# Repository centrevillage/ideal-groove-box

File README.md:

# ideal-groove-box
The GrooveBox for me, and everyone.

~~下記ページに開発Slackの招待リンクがあります。~~
~~どなたでもご自由にご参加ください！~~

~~[開発に参加する方へ](https://github.com/centrevillage/ideal-groove-box/wiki/%E9%96%8B%E7%99%BA%E3%81%AB%E5%8F%82%E5%8A%A0%E3%81%99%E3%82%8B%E6%96%B9%E3%81%B8)~~

2024年12月よりdiscordにてプロジェクト再始動しました。

[ideal groove box project](https://discord.gg/Y8a6y2wYff)

設計思想も変わっているので、こちらのリポジトリはどこかのタイミングで整理する予定です。

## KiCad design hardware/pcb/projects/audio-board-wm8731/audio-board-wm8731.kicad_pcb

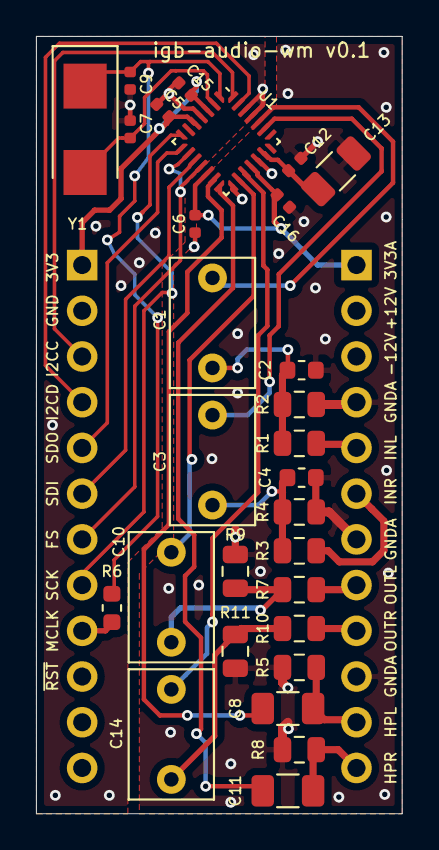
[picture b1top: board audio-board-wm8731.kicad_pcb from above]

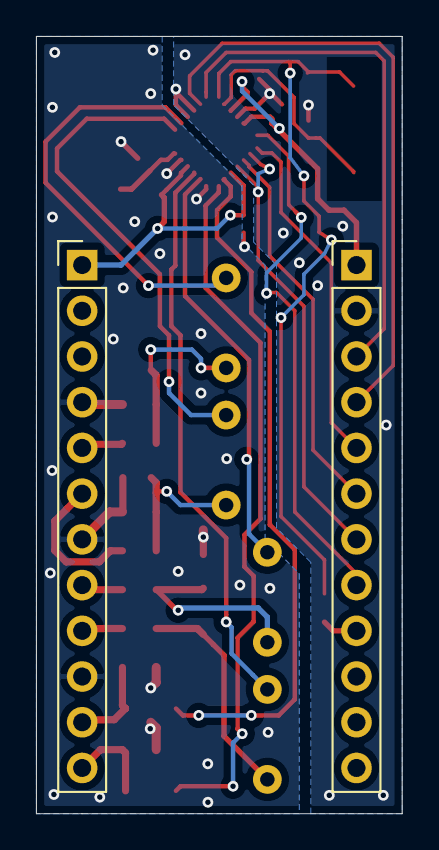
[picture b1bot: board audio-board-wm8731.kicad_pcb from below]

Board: 2 copper layers, 20.3 x 43.2 mm, 31 parts (2 on the bottom side), 30 nets.

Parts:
C1, C3, C10, C14: 1u; C_Rect_L7.0mm_W4.5mm_P5.00mm
C2, C4: 220p; C_0603_1608Metric
C5, C6, C12, C15, C16: 100n; C_0402_1005Metric
C7, C9: 18p; C_0402_1005Metric
C8, C11: 100u; C_1206_3216Metric
C13: 10u; C_1206_3216Metric
J1, J2: Conn_01x12; PinHeader_1x12_P2.54mm_Vertical
R1, R2, R3, R4: 10k; R_0805_2012Metric
R5, R8, R9, R11: 100k; R_0805_2012Metric
R6: 0; R_0603_1608Metric
R7, R10: 100; R_0805_2012Metric
U1: wm8731_qfn; QFN-28_4x4mm_P0.5mm
Y1: 12.288MHz; Crystal_SMD_Abracon_ABM3-2pin_5.0x3.2mm_hand

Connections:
+3.3VA: C6.2, C16.2, J1.1, U1.12, U1.18
+3V3: C5.2, C15.2, J2.1, U1.3, U1.5
/ADC_L: C1.2, U1.24
/ADC_R: C3.2, U1.23
/DAC_L: C10.2, U1.16
/DAC_R: C14.2, U1.17
/HP_OUT_L: C8.2, J1.11, R5.2
/HP_OUT_R: C11.2, J1.12, R8.2
/I2C_SCL: J2.3, U1.28
/I2C_SDA: J2.4, U1.27
/I2S_FS: J2.7, U1.9, U1.11
/I2S_MCLK: J2.9, R6.1
/I2S_SCK: J2.8, U1.7
/I2S_SDI: J2.6, U1.10
/I2S_SDO: J2.5, U1.8
/LINE_IN_L: J1.5, R1.2
/LINE_IN_R: J1.6, R3.2
/LINE_OUT_L: J1.8, R7.2
/LINE_OUT_R: J1.9, R10.2
GND: C5.1, C7.2, C9.2, C15.1, J2.2, U1.4, U1.25, U1.26
GNDA: C2.1, C4.1, C6.1, C12.2, C13.2, C16.1, J1.4, J1.7, J1.10, R2.2, R4.2, R5.1, R8.1, R9.1, R11.1, U1.15, U1.19
unnamed: C1.1, C2.2, R1.1, R2.1
unnamed: C3.1, C4.2, R3.1, R4.1
unnamed: C7.1, U1.2, Y1.2
unnamed: C8.1, U1.13
unnamed: C9.1, R6.2, U1.1, Y1.1
unnamed: C10.1, R7.1, R9.2
unnamed: C11.1, U1.14
unnamed: C12.1, C13.1, U1.20
unnamed: C14.1, R10.1, R11.2

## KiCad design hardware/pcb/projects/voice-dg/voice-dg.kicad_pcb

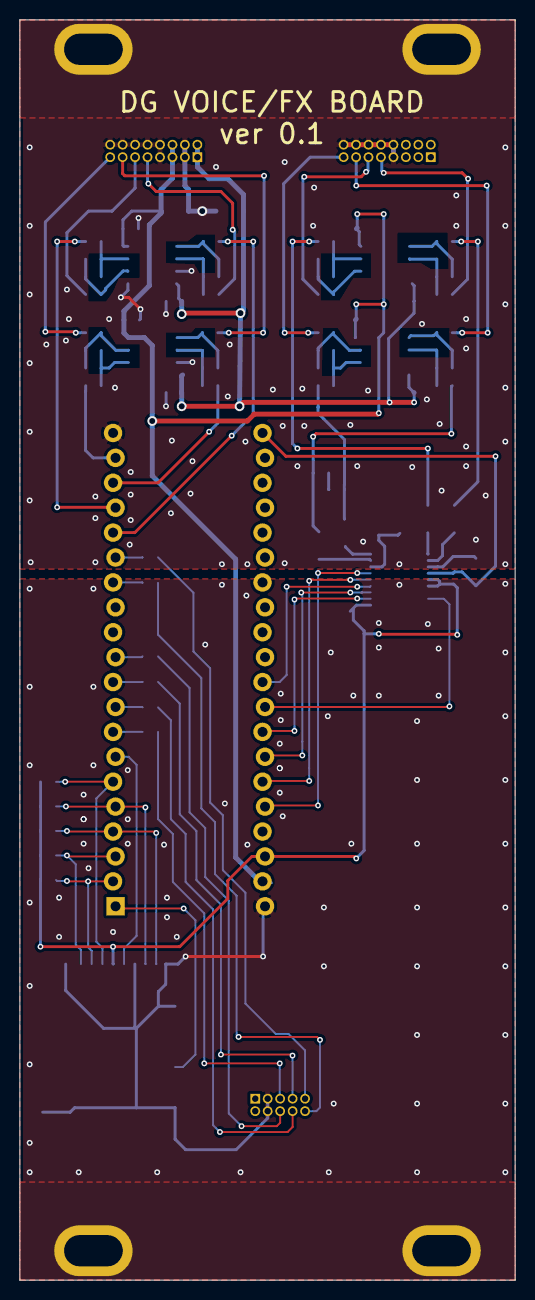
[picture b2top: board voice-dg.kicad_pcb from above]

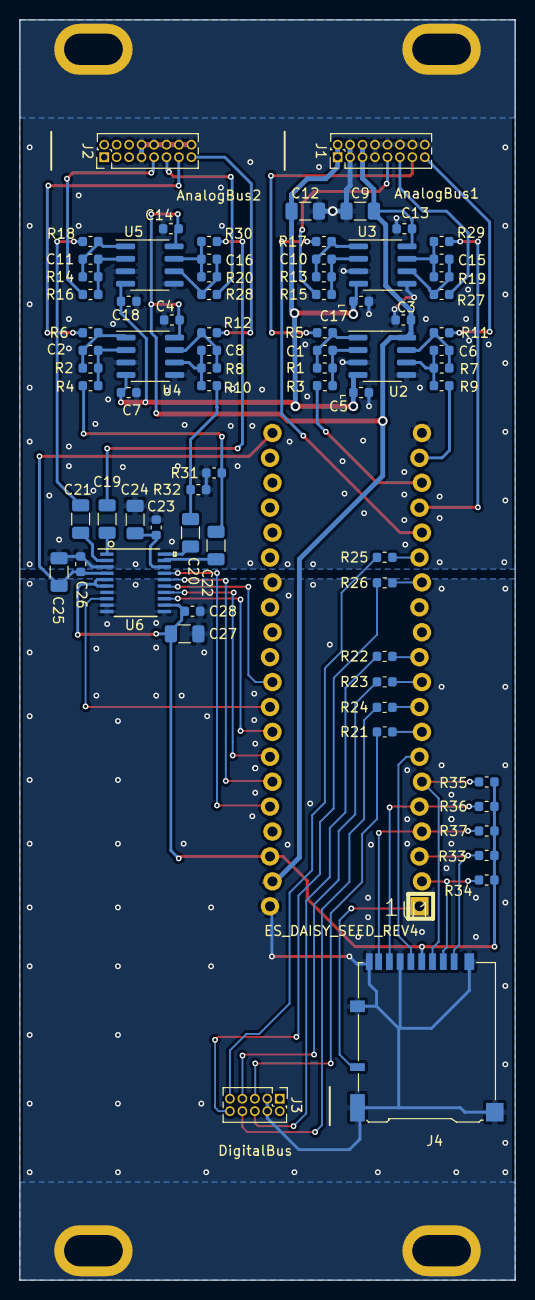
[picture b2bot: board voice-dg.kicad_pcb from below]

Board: 2 copper layers, 50.5 x 128.5 mm, 75 parts (75 on the bottom side), 68 nets.

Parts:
C1, C2, C6, C8, C10, C11, C15, C16: 12p; C_0603_1608Metric
C3, C4, C5, C7, C13, C14, C17, C18, C23, C26, C28: 100n; C_0603_1608Metric
C9, C12: 22u; C_1206_3216Metric
C19, C20, C21, C22, C25, C27: 10u; C_1206_3216Metric
C24: 2.2u; C_1206_3216Metric
J1: AnalogBus; PinHeader_2x08_P1.27mm_Vertical
J2: AnalogBusEx; PinHeader_2x08_P1.27mm_Vertical
J3: DigitalBus; PinHeader_2x05_P1.27mm_Vertical
J4: Micro_SD_Card_Det_Hirose_DM3AT; microSD_HC_Hirose_DM3AT-SF-PEJM5_hand
R1, R2, R7, R8, R15, R16, R27, R28: 100k; R_0603_1608Metric
R3, R4, R9, R10, R13, R14, R19, R20: 10k; R_0603_1608Metric
R5, R6, R11, R12, R17, R18, R29, R30: 470; R_0603_1608Metric
R21, R22, R23, R24, R25, R26: 47; R_0603_1608Metric
R31, R32, R33, R34, R35, R36, R37: 47k; R_0603_1608Metric
U1: ES_DAISY_SEED_REV4; ES_DAISY_SEED
U2, U3, U4, U5: OPA2134; SOIC-8_3.9x4.9mm_P1.27mm
U6: AK4556VT

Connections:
+3.3VA: C25.2, C26.1, U1.21, U6.4
+3V3: C27.2, C28.1, J4.4, R33.2, R34.2, R35.2, R36.2, R37.2, U1.38, U6.5, U6.6, U6.12
+12V: C3.1, C4.1, C9.2, C13.1, C14.1, J1.5, J1.6, U1.39, U2.8, U3.8, U4.8, U5.8
-12V: C5.1, C7.1, C12.1, C17.1, C18.1, J1.1, J1.2, U2.4, U3.4, U4.4, U5.4
/AK4556_RST: U1.36, U6.17
/AnalogIn1: J1.9, R15.2
/AnalogIn2: J1.11, R27.2
/AnalogIn3: J2.9, R16.2
/AnalogIn4: J2.11, R28.2
/AnalogOut1: J1.13, R5.1
/AnalogOut2: J1.15, R11.1
/AnalogOut3: J2.13, R6.1
/AnalogOut4: J2.15, R12.1
/DG_AUDIO_IN_L: R17.1, U1.16
/DG_AUDIO_IN_R: R29.1, U1.17
/DG_AUDIO_OUT_L: R3.2, U1.18
/DG_AUDIO_OUT_R: R9.2, U1.19
/EX_AUDIO_IN_L: C21.1, R18.1
/EX_AUDIO_IN_R: C19.1, R30.1
/EX_AUDIO_OUT_L: C22.2, R4.2, R31.2
/EX_AUDIO_OUT_R: C20.2, R10.2, R32.2
/SAI2_FS_B: U1.34, U6.14
/SAI2_MCLK_B: U1.31, U6.15
/SAI2_SCK_B: U1.35, U6.16
/SAI2_SD_A: U1.33, U6.13
/SAI2_SD_B: U1.32, U6.8
/SD_CLK: J4.5, U1.7
/SD_CMD: J4.3, R35.1, U1.6
/SD_D0: J4.7, R36.1, U1.5
/SD_D1: J4.8, R37.1, U1.4
/SD_D2: J4.1, R33.1, U1.3
/SD_D3: J4.2, R34.1, U1.2
/SPI_MISO: R23.2, U1.10
/SPI_MOSI: R22.1, U1.11
/SPI_SCK: R24.1, U1.9
/USART_RX: R25.2, U1.15
/USART_TX: R26.1, U1.14
/~SD_SW: J4.10, U1.1
/~SPI_CS: R21.2, U1.8
GND: C27.1, C28.2, J3.3, J3.4, J4.6, J4.9, J4.11, U1.40, U6.7, U6.9, U6.10, U6.11
GNDA: C3.2, C4.2, C5.2, C7.2, C9.1, C12.2, C13.2, C14.2, C17.2, C18.2, C23.2, C24.1, C25.1, C26.2, J1.3, J1.4, J1.7, J1.8, J1.10, J1.12, J1.14, J1.16, J2.7, J2.8, J2.10, J2.12, J2.14, J2.16, R31.1, R32.1, U1.20, U2.3, U2.5, U3.3, U3.5, U4.3, U4.5, U5.3, U5.5, U6.3
unnamed: C1.1, R1.1, R5.2, U2.1
unnamed: C1.2, R1.2, R3.1, U2.2
unnamed: C2.1, R2.1, R6.2, U4.1
unnamed: C2.2, R2.2, R4.1, U4.2
unnamed: C6.1, R7.1, R11.2, U2.7
unnamed: C6.2, R7.2, R9.1, U2.6
unnamed: C8.1, R8.1, R12.2, U4.7
unnamed: C8.2, R8.2, R10.1, U4.6
unnamed: C10.1, R13.1, R17.2, U3.1
unnamed: C10.2, R13.2, R15.1, U3.2
unnamed: C11.1, R14.1, R18.2, U5.1
unnamed: C11.2, R14.2, R16.1, U5.2
unnamed: C15.1, R19.1, R29.2, U3.7
unnamed: C15.2, R19.2, R27.1, U3.6
unnamed: C16.1, R20.1, R30.2, U5.7
unnamed: C16.2, R20.2, R28.1, U5.6
unnamed: C19.2, U6.1
unnamed: C20.1, U6.20
unnamed: C21.2, U6.2
unnamed: C22.1, U6.19
unnamed: C23.1, C24.2, U6.18
unnamed: J3.5, R21.1
unnamed: J3.6, R22.2
unnamed: J3.7, R23.1
unnamed: J3.8, R24.2
unnamed: J3.9, R25.1
unnamed: J3.10, R26.2

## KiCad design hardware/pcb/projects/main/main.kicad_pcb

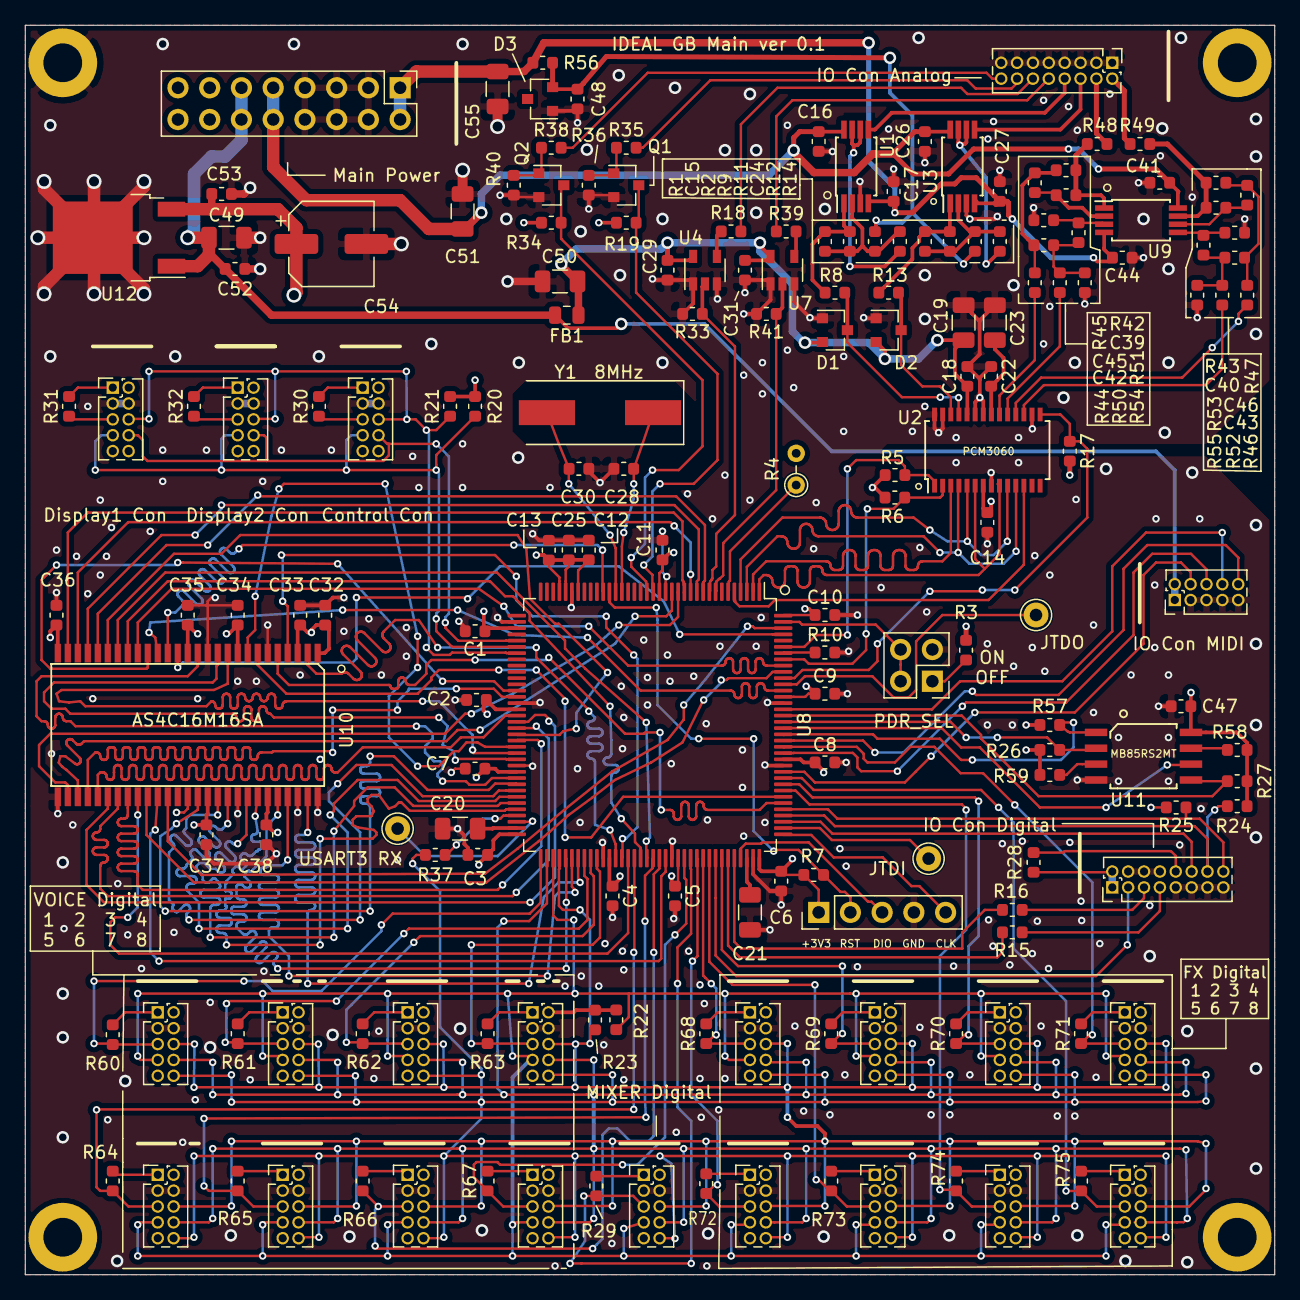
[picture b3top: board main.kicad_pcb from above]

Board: 4 copper layers, 100.0 x 100.0 mm, 176 parts (0 on the bottom side), 154 nets.

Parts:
C1, C2, C3, C4, C5, C6, C7, C8, C9, C10, C11, C12, C13, C14, C16, C17, C18, C22, C25, C26, C27, C29, C31, C32, C33, C34, C35, C36, C37, C38, C41, C44, C47, C48, C52, C53: 100n; C_0603_1608Metric
C15, C24, C28, C30: 18p; C_0603_1608Metric
C19, C23: 10u; C_1206_3216Metric
C20, C21: 2.2u; C_1206_3216Metric
C39, C40, C45, C46: 470p; C_0603_1608Metric
C42, C43: 2.2n; C_0603_1608Metric
C49, C50, C51, C55: 22u; C_1206_3216Metric
C54: 100u; CP_Elec_6.3x5.3
D1, D2: BAT54S; SOT-23
D3: LM4040; SOT-23
FB1: Ferrite; R_0805_2012Metric
J1: IO_CON_ANALOG; PinHeader_2x08_P1.27mm_Vertical
J2: PDR_ON_SEL; PinHeader_2x02_P2.54mm_Vertical
J3: VOICE1_DIGITAL; PinHeader_2x05_P1.27mm_Vertical
J4: FX1_DIGITAL; PinHeader_2x05_P1.27mm_Vertical
J5: VOICE5_DIGITAL; PinHeader_2x05_P1.27mm_Vertical
J6: FX5_DIGITAL; PinHeader_2x05_P1.27mm_Vertical
J7: VOICE2_DIGITAL; PinHeader_2x05_P1.27mm_Vertical
J8: FX2_DIGITAL; PinHeader_2x05_P1.27mm_Vertical
J9: VOICE6_DIGITAL; PinHeader_2x05_P1.27mm_Vertical
J10: FX6_DIGITAL; PinHeader_2x05_P1.27mm_Vertical
J11: VOICE3_DIGITAL; PinHeader_2x05_P1.27mm_Vertical
J12: FX3_DIGITAL; PinHeader_2x05_P1.27mm_Vertical
J13: VOICE7_DIGITAL; PinHeader_2x05_P1.27mm_Vertical
J14: FX7_DIGITAL; PinHeader_2x05_P1.27mm_Vertical
J15: IO_CON_MIDI; PinHeader_2x05_P1.27mm_Vertical
J16: VOICE4_DIGITAL; PinHeader_2x05_P1.27mm_Vertical
J17: FX4_DIGITAL; PinHeader_2x05_P1.27mm_Vertical
J18: VOICE8_DIGITAL; PinHeader_2x05_P1.27mm_Vertical
J19: FX8_DIGITAL; PinHeader_2x05_P1.27mm_Vertical
J20: SWD_CON; PinHeader_1x05_P2.54mm_Vertical
J21: MIXER_DIGITAL; PinHeader_2x05_P1.27mm_Vertical
J22: DISPLAY1_DIGITAL; PinHeader_2x05_P1.27mm_Vertical
J23: IO_CON_DIGITAL; PinHeader_2x08_P1.27mm_Vertical
J24: POWER_CON; PinHeader_2x08_P2.54mm_Vertical
J25: CONTROL_DIGTAL; PinHeader_2x05_P1.27mm_Vertical
J26: DISPLAY2_DIGITAL; PinHeader_2x05_P1.27mm_Vertical
Q1, Q2: MMBT3904; SOT-23
R1, R11: 30k; R_0603_1608Metric
R2, R12: 120k; R_0603_1608Metric
R3, R5, R6, R7, R10, R17, R19, R20, R21, R22, R23, R24, R25, R26, R27, R28, R29, R30, R31, R32, R33, R34, R41, R57, R58, R59, R60, R61, R62, R63, R64, R65, R66, R67, R68, R69, R70, R71, R72, R73, R74, R75: 10k; R_0603_1608Metric
R4: 0; R_Axial_DIN0204_L3.6mm_D1.6mm_P2.54mm_Vertical
R8, R13, R48, R49: 470; R_0603_1608Metric
R9, R14: 200k; R_0603_1608Metric
R15, R16, R37: 10; R_0603_1608Metric
R18, R39, R45, R47, R51, R53: 1k; R_0603_1608Metric
R35, R36, R38, R40: 100k; R_0603_1608Metric
R42, R43, R54, R55: 12k; R_0603_1608Metric
R44, R46, R50, R52: 4.7k; R_0603_1608Metric
R56: 3.3k; R_0603_1608Metric
TP1: JTDI; Pin_D1.0mm_L10.0mm
TP2: JTDO; Pin_D1.0mm_L10.0mm
TP3: USART3_RX; Pin_D1.0mm_L10.0mm
U1, U3, U9: TL072; TSSOP-8_4.4x3mm_P0.65mm
U2: PCM3060; TSSOP-28_4.4x9.7mm_P0.65mm
U4, U7: 74AHCT1G125; SOT-23-5
U8: STM32F446ZETx; LQFP-144_20x20mm_P0.5mm
U10: AS4C16M16SA
U11: MB85RS2MT
U12: L7803; TO-252-2
Y1: 8MHz; Crystal_SMD_HC49-SD

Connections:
+3V3: C1.1, C2.1, C3.1, C4.1, C5.1, C6.1, C7.1, C8.1, C9.1, C10.1, C11.1, C12.1, C13.1, C14.1, C25.1, C32.1, C33.1, C34.1, C35.1, C36.1, C37.1, C38.1, C47.2, C53.1, C54.1, J3.1, J3.2, J4.1, J4.2, J5.1, J5.2, J6.1, J6.2, J7.1, J7.2, J8.1, J8.2, J9.1, J9.2, J10.1, J10.2, J11.1, J11.2, J12.1, J12.2, J13.1, J13.2, J14.1, J14.2, J16.1, J16.2, J17.1, J17.2, J18.1, J18.2, J19.1, J19.2, J20.1, J21.1, J21.2, J22.1, J22.2, J23.1, J23.2, J25.1, J25.2, J26.1, J26.2, R3.2, R4.2, R5.2, R6.2, R7.2, R17.2, R19.1, R20.2, R21.2, R22.2, R23.2, R24.2, R25.2, R26.2, R27.2, R28.2, R29.2, R30.2, R31.2, R32.2, R34.1, R57.2, R58.2, R59.2, R60.2, R61.2, R62.2, R63.2, R64.2, R65.2, R66.2, R67.2, R68.2, R69.2, R70.2, R71.2, R72.2, R73.2, R74.2, R75.2, U2.7, U8.17, U8.30, U8.32, U8.33, U8.39, U8.52, U8.62, U8.72, U8.84, U8.95, U8.108, U8.121, U8.131, U8.144, U10.1, U10.3, U10.9, U10.14, U10.27, U10.43, U10.49, U11.8, U12.3
+5V: C49.1, C52.1, FB1.2, J15.1, J15.2, J24.11, J24.12, U12.1
+5VA: C18.1, C19.1, C29.1, C31.1, C50.1, D1.2, D2.2, FB1.1, U2.24, U4.5, U7.5
+12V: C16.1, C26.1, C41.1, C51.1, J24.9, J24.10, U1.8, U3.8, U9.8
-12V: C17.2, C27.2, C44.2, C55.2, J24.1, J24.2, R56.2, U1.4, U3.4, U9.4
/FMC_A0: U8.10, U10.23
/FMC_A1: U8.11, U10.24
/FMC_A2: U8.12, U10.25
/FMC_A3: U8.13, U10.26
/FMC_A4: U8.14, U10.29
/FMC_A5: U8.15, U10.30
/FMC_A6: U8.50, U10.31
/FMC_A7: U8.53, U10.32
/FMC_A8: U8.54, U10.33
/FMC_A9: U8.55, U10.34
/FMC_A10: U8.56, U10.22
/FMC_A11: U8.57, U10.35
/FMC_A12: U8.87, U10.36
/FMC_BA0: U8.89, U10.20
/FMC_BA1: U8.90, U10.21
/FMC_D0: U8.85, U10.2
/FMC_D1: U8.86, U10.4
/FMC_D2: U8.114, U10.5
/FMC_D3: U8.115, U10.7
/FMC_D4: U8.58, U10.8
/FMC_D5: U8.59, U10.10
/FMC_D6: U8.60, U10.11
/FMC_D7: U8.63, U10.13
/FMC_D8: U8.64, U10.42
/FMC_D9: U8.65, U10.44
/FMC_D10: U8.66, U10.45
/FMC_D11: U8.67, U10.47
/FMC_D12: U8.68, U10.48
/FMC_D13: U8.77, U10.50
/FMC_D14: U8.78, U10.51
/FMC_D15: U8.79, U10.53
/FMC_NBL0: U8.141, U10.15
/FMC_NBL1: U8.142, U10.39
/FMC_SDCKE1: U8.135, U10.37
/FMC_SDCLK: U8.93, U10.38
/FMC_SDNCAS: U8.132, U10.17
/FMC_SDNE1: U8.136, U10.19
/FMC_SDNRAS: U8.49, U10.18
/FMC_SDNWE: U8.26, U10.16
/I2C_SCL: R5.1, U2.1, U8.139
/I2C_SDA: R6.1, U2.2, U8.137
/OTG_FS_DM: J23.7, R15.1
/OTG_FS_DP: J23.5, R16.1
/OTG_FS_VBUS: J23.3, U8.101
/SAI1_FS_A: U2.4, U2.11, U8.3
/SAI1_MCLK_A: U2.6, U2.9, U8.1
/SAI1_SCK_A: U2.5, U2.10, U8.4
/SAI1_SD_A: U2.12, U8.5
/SAI1_SD_B: U2.3, U8.2
/SPI1_MISO: J22.7, J25.7, J26.7, R20.1, U8.42
/SPI1_MOSI: J22.6, J25.6, J26.6, R21.1, U8.43
/SPI1_SCK: J22.8, J25.8, J26.8, U8.41
/SPI2_MISO: J3.7, J4.7, J5.7, J6.7, J7.7, J8.7, J9.7, J10.7, J11.7, J12.7, J13.7, J14.7, J16.7, J17.7, J18.7, J19.7, J21.7, R22.1, U8.75
/SPI2_MOSI: J3.6, J4.6, J5.6, J6.6, J7.6, J8.6, J9.6, J10.6, J11.6, J12.6, J13.6, J14.6, J16.6, J17.6, J18.6, J19.6, J21.6, R23.1, U8.76
/SPI2_SCK: J3.8, J4.8, J5.8, J6.8, J7.8, J8.8, J9.8, J10.8, J11.8, J12.8, J13.8, J14.8, J16.8, J17.8, J18.8, J19.8, J21.8, U8.74
/SPI3_MISO: J23.14, R24.1, U8.112
/SPI3_MOSI: J23.16, R25.1, U8.113
/SPI3_SCK: J23.12, U8.111
/SPI4_MISO: R26.1, U8.127, U11.2
/SPI4_MOSI: R27.1, U8.128, U11.5
/SPI4_SCK: U8.126, U11.6
/SWCLK: J20.5, U8.109
/SWDIO: J20.3, U8.105
/USART2_RX: J15.6, U8.122
/USART2_TX: J15.4, U8.119
/USART3_TX: J3.10, J4.10, J5.10, J6.10, J7.10, J8.10, J9.10, J10.10, J11.10, J12.10, J13.10, J14.10, J16.10, J17.10, J18.10, J19.10, J21.10, R37.1
/USART6_RX: J15.10, U8.124
/USART6_TX: J15.8, U8.129
/~CONTROL_SPI_CS: J25.5, R30.1
/~DAC_RESET: R17.1, U2.15, U8.134
/~DISPLAY1_SPI_CS: J22.5, R31.1
/~DISPLAY2_SPI_CS: J26.5, R32.1
/~FRAM_SPI_CS: R57.1, U8.125, U11.1
/~FX1_SPI_CS: J4.5, R68.1, U8.99
/~FX2_SPI_CS: J8.5, R69.1, U8.102
/~FX3_SPI_CS: J12.5, R70.1, U8.117
/~FX4_SPI_CS: J17.5, R71.1, U8.123
/~FX5_SPI_CS: J6.5, R72.1, U8.98
/~FX6_SPI_CS: J10.5, R73.1, U8.100
/~FX7_SPI_CS: J14.5, R74.1, U8.116
/~FX8_SPI_CS: J19.5, R75.1, U8.118
/~MIXER_SPI_CS: J21.5, R29.1, U8.97
/~RESET: J20.2, R7.1, U8.25
/~SD_SPI_CS: J23.10, R28.1
/~VOICE1_SPI_CS: J3.5, R60.1, U8.73
/~VOICE2_SPI_CS: J7.5, R61.1, U8.80
/~VOICE3_SPI_CS: J11.5, R62.1, U8.81
/~VOICE4_SPI_CS: J16.5, R63.1, U8.82
/~VOICE5_SPI_CS: J5.5, R64.1, U8.88
/~VOICE6_SPI_CS: J9.5, R65.1, U8.91
/~VOICE7_SPI_CS: J13.5, R66.1, U8.92
/~VOICE8_SPI_CS: J18.5, R67.1, U8.96
CV1_IN: J1.8, U1.5
CV1_OUT: J1.4, R48.2
CV2_IN: J1.6, U3.5
CV2_OUT: J1.2, R49.2
DAC_IN_L: D1.3, R8.1, U2.25
DAC_IN_R: D2.3, R13.1, U2.26
DAC_VOUTL+: R44.1, U2.20
DAC_VOUTL-: R50.1, U2.19
DAC_VOUTR+: R46.1, U2.18
DAC_VOUTR-: R52.1, U2.17
GATE1_IN: J1.16, R38.2
GATE1_IN_BUF_OUT: Q2.3, R34.2, U8.19
GATE1_OUT: J1.12, R18.1
GATE1_OUT_BUF_IN: R33.1, U4.2, U8.9
GATE2_IN: J1.14, R35.2
GATE2_IN_BUF_OUT: Q1.3, R19.2, U8.18
GATE2_OUT: J1.10, R39.1
GATE2_OUT_BUF_IN: R41.1, U7.2, U8.8
GND: C1.2, C2.2, C3.2, C4.2, C5.2, C6.2, C7.2, C8.2, C9.2, C10.2, C11.2, C12.2, C13.2, C14.2, C16.2, C17.1, C18.2, C19.2, C20.2, C21.2, C22.1, C23.1, C25.2, C26.2, C27.1, C28.2, C29.2, C30.2, C31.2, C32.2, C33.2, C34.2, C35.2, C36.2, C37.2, C38.2, C41.2, C44.1, C45.1, C46.1, C47.1, C48.2, C49.2, C50.2, C51.2, C52.2, C53.2, C54.2, C55.1, D1.1, D2.1, D3.1, J1.1, J1.3, J1.5, J1.7, J1.9, J1.11, J1.13, J1.15, J2.3, J3.3, J3.4, J4.3, J4.4, J5.3, J5.4, J6.3, J6.4, J7.3, J7.4, J8.3, J8.4, J9.3, J9.4, J10.3, J10.4, J11.3, J11.4, J12.3, J12.4, J13.3, J13.4, J14.3, J14.4, J15.3, J15.5, J15.7, J15.9, J16.3, J16.4, J17.3, J17.4, J18.3, J18.4, J19.3, J19.4, J20.4, J21.3, J21.4, J22.3, J22.4, J23.4, J23.6, J23.8, J23.9, J23.11, J23.13, J23.15, J24.3, J24.4, J24.5, J24.6, J24.7, J24.8, J25.3, J25.4, J26.3, J26.4, Q1.2, Q2.2, R10.2, R33.2, R36.2, R40.2, R41.2, R54.1, R55.1, U1.3, U2.8, U2.16, U2.22, U2.23, U2.27, U2.28, U3.3, U4.1, U4.3, U7.1, U7.3, U8.16, U8.31, U8.38, U8.51, U8.61, U8.83, U8.94, U8.107, U8.120, U8.130, U10.6, U10.12, U10.28, U10.41, U10.46, U10.52, U10.54, U11.4, U12.2
unnamed: C15.1, R1.2, R2.1, R9.1, U1.2
unnamed: C15.2, R1.1, R8.2, U1.1
unnamed: C20.1, U8.71
unnamed: C21.1, U8.106
unnamed: C22.2, C23.2, U2.21
unnamed: C24.1, R11.2, R12.1, R14.1, U3.2
unnamed: C24.2, R11.1, R13.2, U3.1
unnamed: C28.1, U8.23, Y1.1
unnamed: C30.1, U8.24, Y1.2
unnamed: C39.1, R45.2, U9.2
unnamed: C39.2, R42.2, R48.1, U9.1
unnamed: C40.1, R47.2, U9.6
unnamed: C40.2, R43.2, R49.1, U9.7
unnamed: C42.1, R42.1, R44.2, R45.1
unnamed: C42.2, R50.2, R51.1, R54.2
unnamed: C43.1, R43.1, R46.2, R47.1
unnamed: C43.2, R52.2, R53.1, R55.2
unnamed: C45.2, R51.2, U9.3
unnamed: C46.2, R53.2, U9.5
unnamed: J2.1, R3.1
unnamed: J2.2, J2.4, U8.143
unnamed: Q1.1, R35.1, R36.1
unnamed: Q2.1, R38.1, R40.1
unnamed: R4.1, U8.6
unnamed: R9.2, U1.6, U1.7
unnamed: R10.1, U8.138
unnamed: R14.2, U3.6, U3.7
unnamed: R15.2, U8.103
unnamed: R16.2, U8.104
unnamed: R18.2, U4.4
unnamed: R37.2, U8.69
unnamed: R39.2, U7.4
unnamed: R58.1, U11.7
unnamed: R59.1, U11.3
unnamed: TP1.1, U8.110
unnamed: TP2.1, U8.133
unnamed: TP3.1, U8.70
VREF_-10V: C48.1, D3.2, R2.2, R12.2, R56.1

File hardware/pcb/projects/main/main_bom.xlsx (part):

ID | 参照記号 | パッケージ | 数 | 名称 | 精度セイド | 最大電圧/電流/電力サイダイデンアツデンリュウデンリョク | メーカ | 型番カタバン | Digikey | Mouser | Other Supplier
1 | U3,U1,U9 | TSSOP-8_4.4x3mm_P0.65mm | 3 | TL072 |  |  | Texas Instruments | TL072CPWR | https://www.digikey.jp/product-detail/ja/texas-instruments/T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 | https://www.mouser.jp/ProductDetail/Texas-Instruments/TL072C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
2 | U10 | AS4C16M16SA | 1 | AS4C16M16SA |  |  | Alliance Memory | AS4C16M16SA-6TINTR | https://www.digikey.jp/product-detail/ja/alliance-memory-inc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 | https://www.mouser.jp/ProductDetail/Alliance-Memory/AS4C16M1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
3 | C28,C15,C24,C30 | C_0603_1608Metric | 4 | 18p | 1% | 50V | Walsin | 0603N180F500CT | https://www.digikey.jp/product-detail/ja/walsin-technology-c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 | https://www.mouser.jp/ProductDetail/Walsin/0603N180F500CT?qs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
4 | Y1 | Crystal_SMD_HC49-SD | 1 | 8MHz | 30ppm |  | ABRACON | ABLS2-8.000MHZ-D4Y-T | https://www.digikey.jp/product-detail/ja/abracon-llc/ABLS2-8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 | https://www.mouser.jp/ProductDetail/ABRACON/ABLS2-8000MHZ-D4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
5 | R75,R74,R73,R72,R71,R70,R69,R68,R67,R66,R65,R64,R63,R62,R61,R60,R20,R3,R5,R6,R7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 | R_0603_1608Metric | 42 | 10k | 1% | 0.1W | Yageo | RC0603FR-0710KL | https://www.digikey.jp/product-detail/ja/yageo/RC0603FR-0710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 | https://www.mouser.jp/ProductDetail/Yageo/RC0603FR-0710KL?qs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
6 | U8 | LQFP-144_20x20mm_P0.5mm | 1 | STM32F446ZETx |  |  | STMicroelectronics | STM32F446ZET6 | https://www.digikey.jp/products/ja?keywords=STM32F446ZET6 | https://www.mouser.jp/ProductDetail/STMicroelectronics/STM32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
7 | C14,C1,C2,C3,C4,C5,C6,C7,C8,C9,C10,C11,C12,C13,C16,C17,C18,C22,C25,C26,C27,C29,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 | C_0603_1608Metric | 36 | 100n | 10% | 50V | Yageo | CC0603KRX7R9BB104 | https://www.digikey.jp/product-detail/ja/yageo/CC0603KRX7R9B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 | https://www.mouser.jp/ProductDetail/Yageo/CC0603KRX7R9BB104?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
8 | C19,C23 | C_1206_3216Metric | 2 | 10u | 10% | 25V | Taiyo Yuden | TMK316BJ106KL-T | https://www.digikey.jp/product-detail/ja/taiyo-yuden/TMK316B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 | https://www.mouser.jp/ProductDetail/Taiyo-Yuden/TMK316BJ106K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
9 | C20,C21 | C_1206_3216Metric | 2 | 2.2u | 10% | 50V | Taiyo Yuden | UMK316B7225KL-T | https://www.digikey.jp/product-detail/ja/taiyo-yuden/UMK316B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 | https://www.mouser.jp/ProductDetail/Taiyo-Yuden/UMK316B7225K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
10 | C39,C40,C45,C46 | C_0603_1608Metric | 4 | 470p | 1% | 50V | Yageo | CC0603FRNPO9BN471 | https://www.digikey.jp/product-detail/ja/yageo/CC0603FRNPO9B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 | https://www.mouser.jp/ProductDetail/Yageo/CC0603FRNPO9BN471?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
11 | C42,C43 | C_0603_1608Metric | 2 | 2.2n | 1% | 50V | Murata | GRM1885C1H222FA01D | https://www.digikey.jp/product-detail/ja/murata-electronics/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 | https://www.mouser.jp/ProductDetail/Murata-Electronics/GRM18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
12 | C49,C50,C51,C55 | C_1206_3216Metric | 4 | 22u | 20% | 25V | Taiyo Yuden | TMK316BBJ226ML-T | https://www.digikey.jp/product-detail/ja/taiyo-yuden/TMK316B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 | https://www.mouser.jp/ProductDetail/Taiyo-Yuden/TMK316BBJ226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
13 | C54 | CP_Elec_6.3x5.3 | 1 | 100u | 20% | 10V | Nichicon | UWT1A101MCL1GB | https://www.digikey.jp/product-detail/ja/nichicon/UWT1A101MC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 | https://www.mouser.jp/ProductDetail/Nichicon/UWT1A101MCL1GB?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
14 | D1,D2 | SOT-23 | 2 | BAT54S |  | 30V | Diodes Incorporated | BAT54S-7-F | https://www.digikey.jp/product-detail/ja/diodes-incorporated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 | https://www.mouser.jp/ProductDetail/Diodes-Incorporated/BAT5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
15 | D3 | SOT-23 | 1 | LM4040 | 0.1% |  | Texas Instruments | LM4040AIM3-10.0/NOPB | https://www.digikey.jp/product-detail/ja/texas-instruments/L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 | https://www.mouser.jp/ProductDetail/Texas-Instruments/LM4040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
16 | FB1 | R_0805_2012Metric | 1 | Ferrite |  | 2A | Fair-Rite | 2508056017Y2 | https://www.digikey.jp/product-detail/ja/fair-rite-products-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 | https://www.mouser.jp/ProductDetail/Fair-Rite/2508056017Y2?q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
17 | J1 | PinHeader_2x08_P1.27mm_Vertical | 1 | IO_CON_ANALOG |  | 1A | CNC Tech | 3220-16-0100-00 | https://www.digikey.jp/product-detail/ja/cnc-tech/3220-16-01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
18 | J2 | PinHeader_2x02_P2.54mm_Vertical | 1 | PDR_ON_SEL
19 | J3 | PinHeader_2x05_P1.27mm_Vertical | 1 | VOICE1_DIGITAL |  | 1A | CNC Tech | 3220-10-0100-00 | https://www.digikey.jp/product-detail/ja/cnc-tech/3220-10-01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
20 | J4 | PinHeader_2x05_P1.27mm_Vertical | 1 | FX1_DIGITAL |  | 1A | CNC Tech | 3220-10-0100-00 | https://www.digikey.jp/product-detail/ja/cnc-tech/3220-10-01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
21 | J5 | PinHeader_2x05_P1.27mm_Vertical | 1 | VOICE5_DIGITAL |  | 1A | CNC Tech | 3220-10-0100-00 | https://www.digikey.jp/product-detail/ja/cnc-tech/3220-10-01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
22 | J6 | PinHeader_2x05_P1.27mm_Vertical | 1 | FX5_DIGITAL |  | 1A | CNC Tech | 3220-10-0100-00 | https://www.digikey.jp/product-detail/ja/cnc-tech/3220-10-01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
23 | J7 | PinHeader_2x05_P1.27mm_Vertical | 1 | VOICE2_DIGITAL |  | 1A | CNC Tech | 3220-10-0100-00 | https://www.digikey.jp/product-detail/ja/cnc-tech/3220-10-01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
24 | J8 | PinHeader_2x05_P1.27mm_Vertical | 1 | FX2_DIGITAL |  | 1A | CNC Tech | 3220-10-0100-00 | https://www.digikey.jp/product-detail/ja/cnc-tech/3220-10-01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
25 | J9 | PinHeader_2x05_P1.27mm_Vertical | 1 | VOICE6_DIGITAL |  | 1A | CNC Tech | 3220-10-0100-00 | https://www.digikey.jp/product-detail/ja/cnc-tech/3220-10-01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
26 | J10 | PinHeader_2x05_P1.27mm_Vertical | 1 | FX6_DIGITAL |  | 1A | CNC Tech | 3220-10-0100-00 | https://www.digikey.jp/product-detail/ja/cnc-tech/3220-10-01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
27 | J11 | PinHeader_2x05_P1.27mm_Vertical | 1 | VOICE3_DIGITAL |  | 1A | CNC Tech | 3220-10-0100-00 | https://www.digikey.jp/product-detail/ja/cnc-tech/3220-10-01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
28 | J12 | PinHeader_2x05_P1.27mm_Vertical | 1 | FX3_DIGITAL |  | 1A | CNC Tech | 3220-10-0100-00 | https://www.digikey.jp/product-detail/ja/cnc-tech/3220-10-01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
29 | J13 | PinHeader_2x05_P1.27mm_Vertical | 1 | VOICE7_DIGITAL |  | 1A | CNC Tech | 3220-10-0100-00 | https://www.digikey.jp/product-detail/ja/cnc-tech/3220-10-01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
30 | J14 | PinHeader_2x05_P1.27mm_Vertical | 1 | FX7_DIGITAL |  | 1A | CNC Tech | 3220-10-0100-00 | https://www.digikey.jp/product-detail/ja/cnc-tech/3220-10-01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
31 | J15 | PinHeader_2x05_P1.27mm_Vertical | 1 | IO_CON_MIDI |  | 1A | CNC Tech | 3220-10-0100-00 | https://www.digikey.jp/product-detail/ja/cnc-tech/3220-10-01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
32 | J16 | PinHeader_2x05_P1.27mm_Vertical | 1 | VOICE4_DIGITAL |  | 1A | CNC Tech | 3220-10-0100-00 | https://www.digikey.jp/product-detail/ja/cnc-tech/3220-10-01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
33 | J17 | PinHeader_2x05_P1.27mm_Vertical | 1 | FX4_DIGITAL |  | 1A | CNC Tech | 3220-10-0100-00 | https://www.digikey.jp/product-detail/ja/cnc-tech/3220-10-01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
34 | J18 | PinHeader_2x05_P1.27mm_Vertical | 1 | VOICE8_DIGITAL |  | 1A | CNC Tech | 3220-10-0100-00 | https://www.digikey.jp/product-detail/ja/cnc-tech/3220-10-01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
35 | J19 | PinHeader_2x05_P1.27mm_Vertical | 1 | FX8_DIGITAL |  | 1A | CNC Tech | 3220-10-0100-00 | https://www.digikey.jp/product-detail/ja/cnc-tech/3220-10-01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
36 | J20 | PinHeader_1x05_P2.54mm_Vertical | 1 | SWD_CON
37 | J21 | PinHeader_2x05_P1.27mm_Vertical | 1 | MIXER_DIGITAL |  | 1A | CNC Tech | 3220-10-0100-00 | https://www.digikey.jp/product-detail/ja/cnc-tech/3220-10-01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
38 | J22 | PinHeader_2x05_P1.27mm_Vertical | 1 | DISPLAY1_DIGITAL |  | 1A | CNC Tech | 3220-10-0100-00 | https://www.digikey.jp/product-detail/ja/cnc-tech/3220-10-01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
39 | J23 | PinHeader_2x08_P1.27mm_Vertical | 1 | IO_CON_DIGITAL |  | 1A | CNC Tech | 3220-16-0100-00 | https://www.digikey.jp/product-detail/ja/cnc-tech/3220-16-01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
40 | J24 | PinHeader_2x08_P2.54mm_Vertical | 1 | POWER_CON |  | 250V/3A | On Shore Technology Inc. | 302-S161 | https://www.digikey.jp/products/ja?keywords=302-S161
41 | J25 | PinHeader_2x05_P1.27mm_Vertical | 1 | CONTROL_DIGTAL |  | 1A | CNC Tech | 3220-10-0100-00 | https://www.digikey.jp/product-detail/ja/cnc-tech/3220-10-01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
42 | J26 | PinHeader_2x05_P1.27mm_Vertical | 1 | DISPLAY2_DIGITAL |  | 1A | CNC Tech | 3220-10-0100-00 | https://www.digikey.jp/product-detail/ja/cnc-tech/3220-10-01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
43 | Q1,Q2 | SOT-23 | 2 | MMBT3904 |  |  | Diodes Incorporated | MMBT3904-7-F | https://www.digikey.jp/product-detail/ja/diodes-incorporated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 | https://www.mouser.jp/ProductDetail/Diodes-Incorporated/MMBT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

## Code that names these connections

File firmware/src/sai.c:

/**
  ******************************************************************************
  * File Name          : SAI.c
  * Description        : This file provides code for the configuration
  *                      of the SAI instances.
  ******************************************************************************
  * @attention
  *
  * <h2><center>&copy; Copyright (c) 2020 STMicroelectronics.
  * All rights reserved.</center></h2>
  *
  * This software component is licensed by ST under BSD 3-Clause license,
  * the "License"; You may not use this file except in compliance with the
  * License. You may obtain a copy of the License at:
  *                        opensource.org/licenses/BSD-3-Clause
  *
  ******************************************************************************
  */
/* Includes ------------------------------------------------------------------*/
#include "sai.h"

#include "gpio.h"
#include "dma.h"

/* USER CODE BEGIN 0 */


/* USER CODE END 0 */

SAI_HandleTypeDef hsai_BlockA1;
SAI_HandleTypeDef hsai_BlockB1;
DMA_HandleTypeDef hdma_sai1_a;
DMA_HandleTypeDef hdma_sai1_b;

/* SAI1 init function */
void MX_SAI1_Init(void)
{

  hsai_BlockA1.Instance = SAI1_Block_A;
  hsai_BlockA1.Init.AudioMode = SAI_MODEMASTER_TX;
  hsai_BlockA1.Init.Synchro = SAI_ASYNCHRONOUS;
  hsai_BlockA1.Init.OutputDrive = SAI_OUTPUTDRIVE_ENABLE;
  hsai_BlockA1.Init.NoDivider = SAI_MASTERDIVIDER_ENABLE;
  hsai_BlockA1.Init.FIFOThreshold = SAI_FIFOTHRESHOLD_1QF;
  hsai_BlockA1.Init.ClockSource = SAI_CLKSOURCE_NA;
  hsai_BlockA1.Init.AudioFrequency = SAI_AUDIO_FREQUENCY_16K;
  hsai_BlockA1.Init.SynchroExt = SAI_SYNCEXT_DISABLE;
  hsai_BlockA1.Init.MonoStereoMode = SAI_STEREOMODE;
  hsai_BlockA1.Init.CompandingMode = SAI_NOCOMPANDING;
  hsai_BlockA1.Init.TriState = SAI_OUTPUT_NOTRELEASED;
  if (HAL_SAI_InitProtocol(&hsai_BlockA1, SAI_I2S_STANDARD, SAI_PROTOCOL_DATASIZE_24BIT, 2) != HAL_OK)
  {
    Error_Handler();
  }

  hsai_BlockB1.Instance = SAI1_Block_B;
  hsai_BlockB1.Init.AudioMode = SAI_MODESLAVE_RX;
  hsai_BlockB1.Init.Synchro = SAI_SYNCHRONOUS;
  hsai_BlockB1.Init.OutputDrive = SAI_OUTPUTDRIVE_ENABLE;
  hsai_BlockB1.Init.FIFOThreshold = SAI_FIFOTHRESHOLD_1QF;
  hsai_BlockB1.Init.SynchroExt = SAI_SYNCEXT_DISABLE;
  hsai_BlockB1.Init.MonoStereoMode = SAI_STEREOMODE;
  hsai_BlockB1.Init.CompandingMode = SAI_NOCOMPANDING;
  hsai_BlockB1.Init.TriState = SAI_OUTPUT_NOTRELEASED;
  if (HAL_SAI_InitProtocol(&hsai_BlockB1, SAI_I2S_STANDARD, SAI_PROTOCOL_DATASIZE_24BIT, 2) != HAL_OK)
  {
    Error_Handler();
  }

}
static uint32_t SAI1_client =0;

void HAL_SAI_MspInit(SAI_HandleTypeDef* hsai)
{

  GPIO_InitTypeDef GPIO_InitStruct;
/* SAI1 */
    if(hsai->Instance==SAI1_Block_A)
    {
    /* SAI1 clock enable */
    if (SAI1_client == 0)
    {
       __HAL_RCC_SAI1_CLK_ENABLE();

    /* Peripheral interrupt init*/
    HAL_NVIC_SetPriority(SAI1_IRQn, 3, 0);
    HAL_NVIC_EnableIRQ(SAI1_IRQn);
    }
    SAI1_client ++;
    
    /**SAI1_A_Block_A GPIO Configuration    
    PE2     ------> SAI1_MCLK_A
    PE4     ------> SAI1_FS_A
    PE5     ------> SAI1_SCK_A
    PE6     ------> SAI1_SD_A 
    */
    GPIO_InitStruct.Pin = GPIO_PIN_2|GPIO_PIN_4|GPIO_PIN_5|GPIO_PIN_6;
    GPIO_InitStruct.Mode = GPIO_MODE_AF_PP;
    GPIO_InitStruct.Pull = GPIO_NOPULL;
    GPIO_InitStruct.Speed = GPIO_SPEED_FREQ_HIGH;
    GPIO_InitStruct.Alternate = GPIO_AF6_SAI1;
    HAL_GPIO_Init(GPIOE, &GPIO_InitStruct);

    /* Peripheral DMA init*/
    
    hdma_sai1_a.Instance = DMA2_Stream1;
    hdma_sai1_a.Init.Channel = DMA_CHANNEL_0;
    hdma_sai1_a.Init.Direction = DMA_MEMORY_TO_PERIPH;
    hdma_sai1_a.Init.PeriphInc = DMA_PINC_DISABLE;
    hdma_sai1_a.Init.MemInc = DMA_MINC_ENABLE;
    hdma_sai1_a.Init.PeriphDataAlignment = DMA_PDATAALIGN_WORD;
    hdma_sai1_a.Init.MemDataAlignment = DMA_MDATAALIGN_WORD;
    hdma_sai1_a.Init.Mode = DMA_CIRCULAR;
    hdma_sai1_a.Init.Priority = DMA_PRIORITY_HIGH;
    hdma_sai1_a.Init.FIFOMode = DMA_FIFOMODE_DISABLE;
    if (HAL_DMA_Init(&hdma_sai1_a) != HAL_OK)
    {
      Error_Handler();
    }

    /* Several peripheral DMA handle pointers point to the same DMA handle.
     Be aware that there is only one stream to perform all the requested DMAs. */
    __HAL_LINKDMA(hsai,hdmarx,hdma_sai1_a);
    __HAL_LINKDMA(hsai,hdmatx,hdma_sai1_a);
    }
    if(hsai->Instance==SAI1_Block_B)
    {
      /* SAI1 clock enable */
      if (SAI1_client == 0)
      {
       __HAL_RCC_SAI1_CLK_ENABLE();

      /* Peripheral interrupt init*/
      HAL_NVIC_SetPriority(SAI1_IRQn, 3, 0);
      HAL_NVIC_EnableIRQ(SAI1_IRQn);
      }
    SAI1_client ++;
    
    /**SAI1_B_Block_B GPIO Configuration    
    PE3     ------> SAI1_SD_B 
    */
    GPIO_InitStruct.Pin = GPIO_PIN_3;
    GPIO_InitStruct.Mode = GPIO_MODE_AF_PP;
    GPIO_InitStruct.Pull = GPIO_NOPULL;
    GPIO_InitStruct.Speed = GPIO_SPEED_FREQ_HIGH;
    GPIO_InitStruct.Alternate = GPIO_AF6_SAI1;
    HAL_GPIO_Init(GPIOE, &GPIO_InitStruct);

    /* Peripheral DMA init*/
    
    hdma_sai1_b.Instance = DMA2_Stream4;
    hdma_sai1_b.Init.Channel = DMA_CHANNEL_1;
    hdma_sai1_b.Init.Direction = DMA_PERIPH_TO_MEMORY;
    hdma_sai1_b.Init.PeriphInc = DMA_PINC_DISABLE;
    hdma_sai1_b.Init.MemInc = DMA_MINC_ENABLE;
    hdma_sai1_b.Init.PeriphDataAlignment = DMA_PDATAALIGN_WORD;
    hdma_sai1_b.Init.MemDataAlignment = DMA_MDATAALIGN_WORD;
    hdma_sai1_b.Init.Mode = DMA_CIRCULAR;
    hdma_sai1_b.Init.Priority = DMA_PRIORITY_HIGH;
    hdma_sai1_b.Init.FIFOMode = DMA_FIFOMODE_DISABLE;
    if (HAL_DMA_Init(&hdma_sai1_b) != HAL_OK)
    {
      Error_Handler();
    }

    /* Several peripheral DMA handle pointers point to the same DMA handle.
     Be aware that there is only one stream to perform all the requested DMAs. */
    __HAL_LINKDMA(hsai,hdmarx,hdma_sai1_b);
    __HAL_LINKDMA(hsai,hdmatx,hdma_sai1_b);
    }
}

void HAL_SAI_MspDeInit(SAI_HandleTypeDef* hsai)
{

/* SAI1 */
    if(hsai->Instance==SAI1_Block_A)
    {
    SAI1_client --;
    if (SAI1_client == 0)
      {
      /* Peripheral clock disable */ 
       __HAL_RCC_SAI1_CLK_DISABLE();
      HAL_NVIC_DisableIRQ(SAI1_IRQn);
      }
    
    /**SAI1_A_Block_A GPIO Configuration    
    PE2     ------> SAI1_MCLK_A
    PE4     ------> SAI1_FS_A
    PE5     ------> SAI1_SCK_A
    PE6     ------> SAI1_SD_A 
    */
    HAL_GPIO_DeInit(GPIOE, GPIO_PIN_2|GPIO_PIN_4|GPIO_PIN_5|GPIO_PIN_6);

    HAL_DMA_DeInit(hsai->hdmarx);
    HAL_DMA_DeInit(hsai->hdmatx);
    }
    if(hsai->Instance==SAI1_Block_B)
    {
    SAI1_client --;
      if (SAI1_client == 0)
      {
      /* Peripheral clock disable */
      __HAL_RCC_SAI1_CLK_DISABLE();
      HAL_NVIC_DisableIRQ(SAI1_IRQn);
      }
    
    /**SAI1_B_Block_B GPIO Configuration    
    PE3     ------> SAI1_SD_B 
    */
    HAL_GPIO_DeInit(GPIOE, GPIO_PIN_3);

    HAL_DMA_DeInit(hsai->hdmarx);
    HAL_DMA_DeInit(hsai->hdmatx);
    }
}

/**
  * @}
  */

/**
  * @}
  */

/************************ (C) COPYRIGHT STMicroelectronics *****END OF FILE****/

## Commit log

2020-02-09 add main pcb project
2020-02-15 add connector margin on pcb layout
2020-02-16 fix pcb layout
2020-02-17 add main bom
2020-02-17 add main bom for digikey
2020-03-17 add todo.txt
2020-06-06 create a scaffold of firmware
2020-06-24 add "DG Voice/FX Board"
2020-06-28 add io-board schematic
2020-07-03 io-board: Change jacks of VOICE/FX from mono to stereo
2021-04-18 add wm8731 audio board
2021-04-21 add core_module4 schematic

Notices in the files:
parts and their libraries:
Copyright 2016 Accelerated Designs. All rights reserved.
